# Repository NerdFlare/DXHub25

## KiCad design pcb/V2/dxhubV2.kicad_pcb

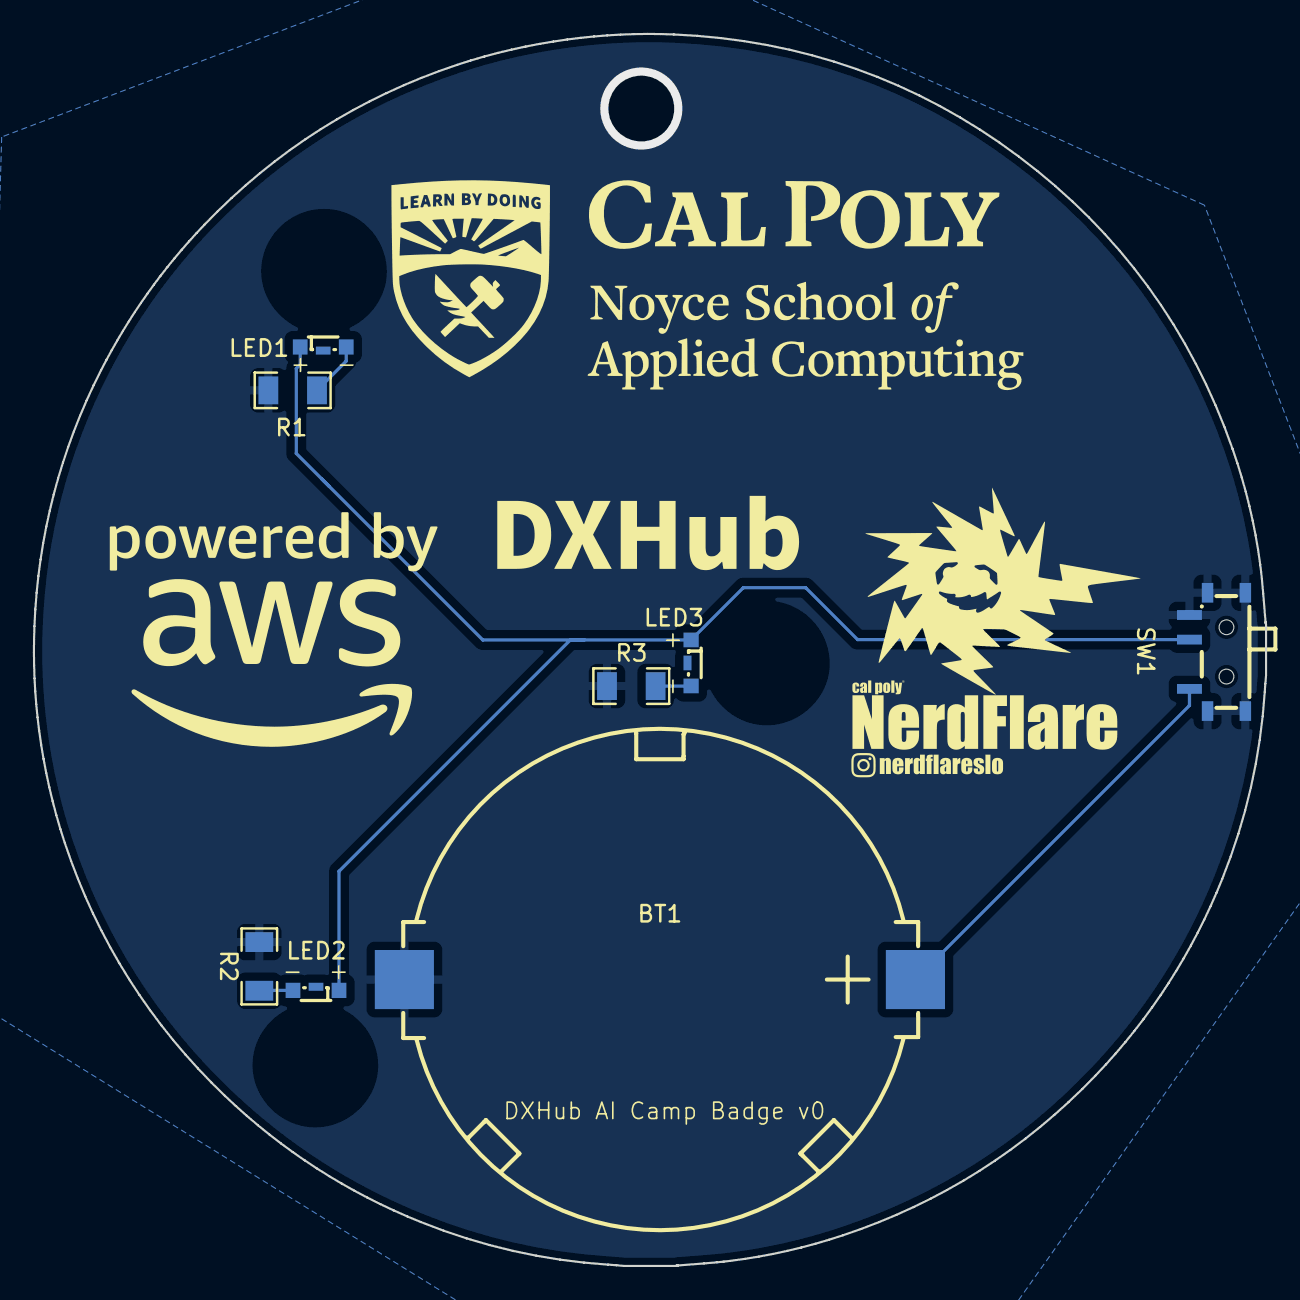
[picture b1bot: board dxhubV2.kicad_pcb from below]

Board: 2 copper layers, 75.0 x 75.0 mm, 8 parts (8 on the bottom side), 6 nets.

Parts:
BT1: BS-24-B4AK014; BAT-SMD_BS-24-B4AK014
LED1, LED2, LED3: XL-3210SYGC; LED-SMD_3P-L3.2-W1.5-RD_YELLOW
R1, R2, R3: 40R; R1206
SW1: MSK12C02; SW-TH_MSK12C02

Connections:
GND: BT1.2, R1.1, R2.1, R3.1, SW1.3, SW1.4
unnamed: BT1.1, SW1.1
unnamed: LED1.1, LED2.1, LED3.1, SW1.2
unnamed: LED1.2, R1.2
unnamed: LED2.2, R2.2
unnamed: LED3.2, R3.2

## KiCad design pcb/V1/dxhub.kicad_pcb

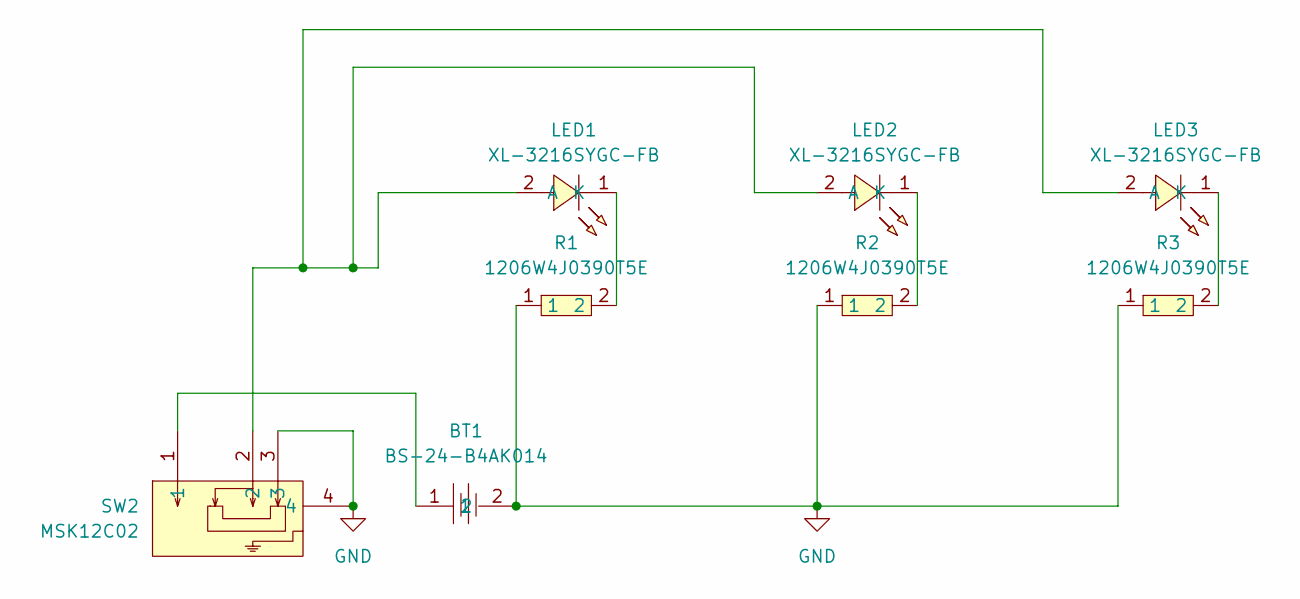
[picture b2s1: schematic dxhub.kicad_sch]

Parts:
BT1: BS-24-B4AK014; BAT-SMD_BS-24-B4AK014; LCSC Part C964813
LED1, LED2, LED3: XL-3216SYGC-FB; LED1206-RD_RED_LTST-C230CKT; LCSC Part C3646940
R1, R2, R3: 1206W4J0390T5E; R1206; LCSC Part C25379
SW2: MSK12C02; SW-TH_MSK12C02; LCSC Part C431540

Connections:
GND: BT1.2, R1.1, R2.1, R3.1, SW2.3, SW2.4
unnamed: BT1.1, SW2.1
unnamed: LED1.2 (A), LED2.2 (A), LED3.2 (A), SW2.2
unnamed: LED1.1 (K), R1.2
unnamed: LED2.1 (K), R2.2
unnamed: LED3.1 (K), R3.2

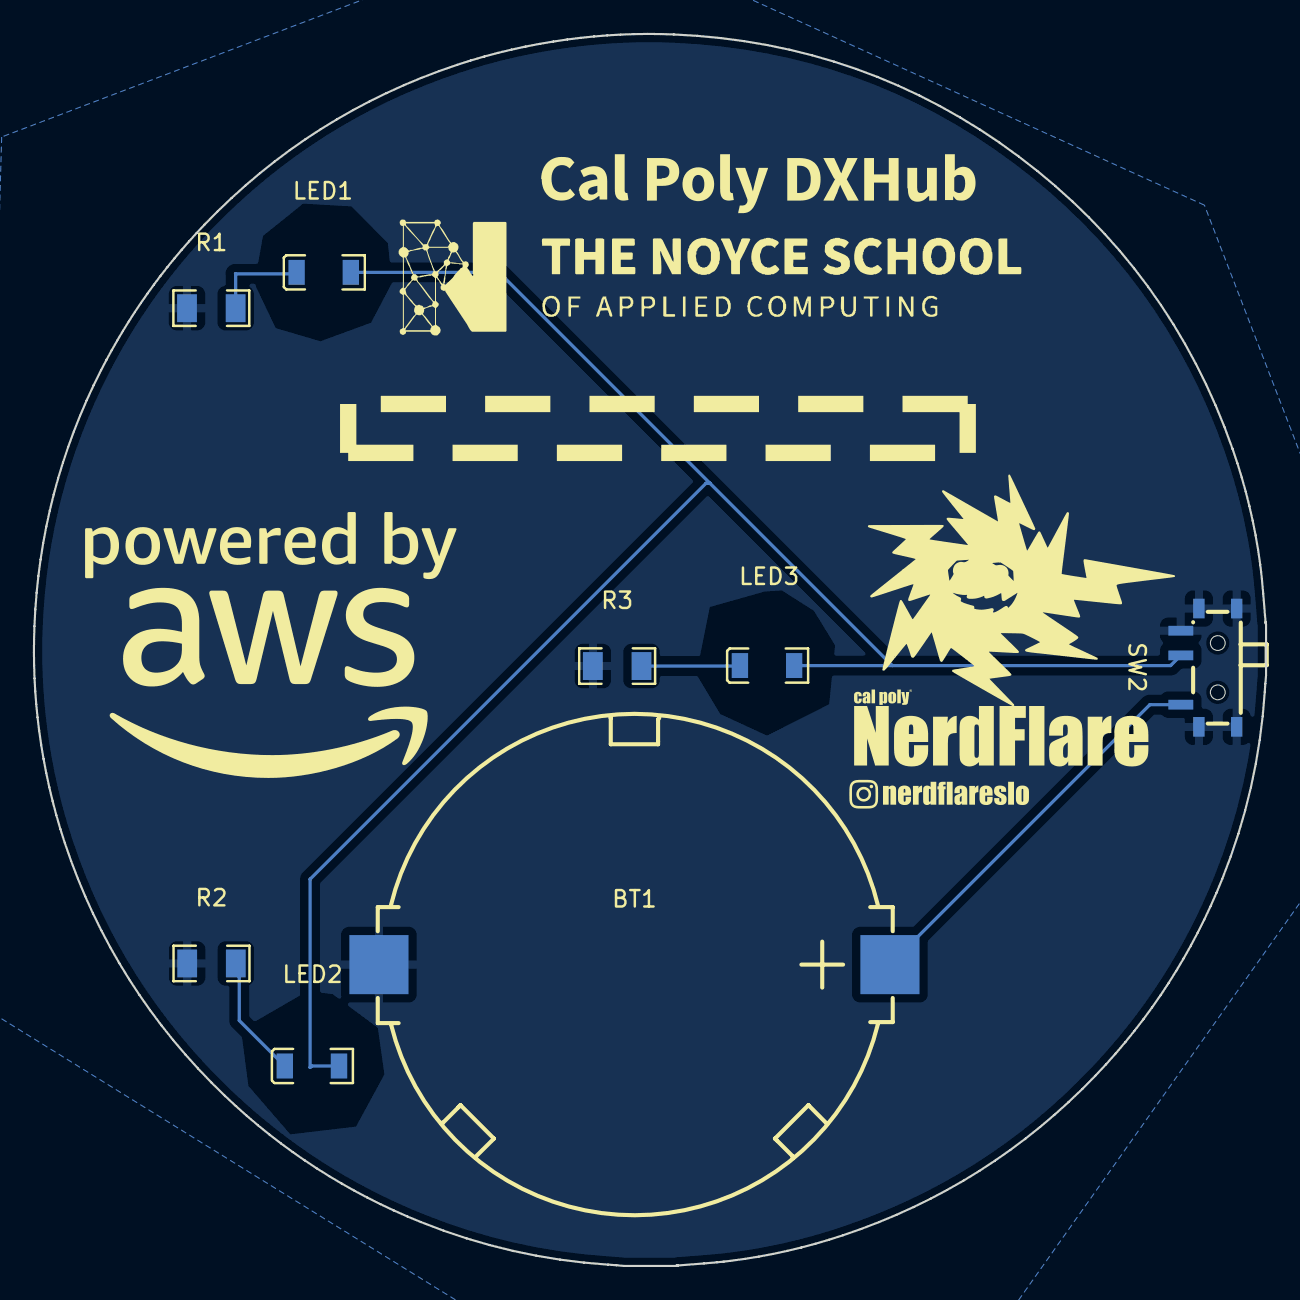
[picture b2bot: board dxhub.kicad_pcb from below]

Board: 2 copper layers, 75.0 x 75.0 mm, 8 parts (8 on the bottom side), 6 nets.

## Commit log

2025-06-09 Added SVGs
2025-06-10 PCB Uploaded
2025-06-10 Finished Design
2025-06-11 EasyEDAFiles
2025-06-11 New NF, Noyce, and DXHub logo; cleaned up copper fills on back; reversed LEDs to match datasheet
2025-06-11 Ready for fab review: Modified LED footprint silk to not; new traces to match datasheet
2025-06-11 moved R1 to make room for pin; added hole for lanyard; increased DXHub logo size
2025-06-12 This is board v0: resized logos; did some rerouting; new gerbers ready for prototype of v0.
